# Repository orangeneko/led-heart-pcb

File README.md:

## About
LED heart. Surprise your soulmate!

## PCB

## Hardware
* MSP430F2370
* FT232RL & micro-usb for programming
* CR2032

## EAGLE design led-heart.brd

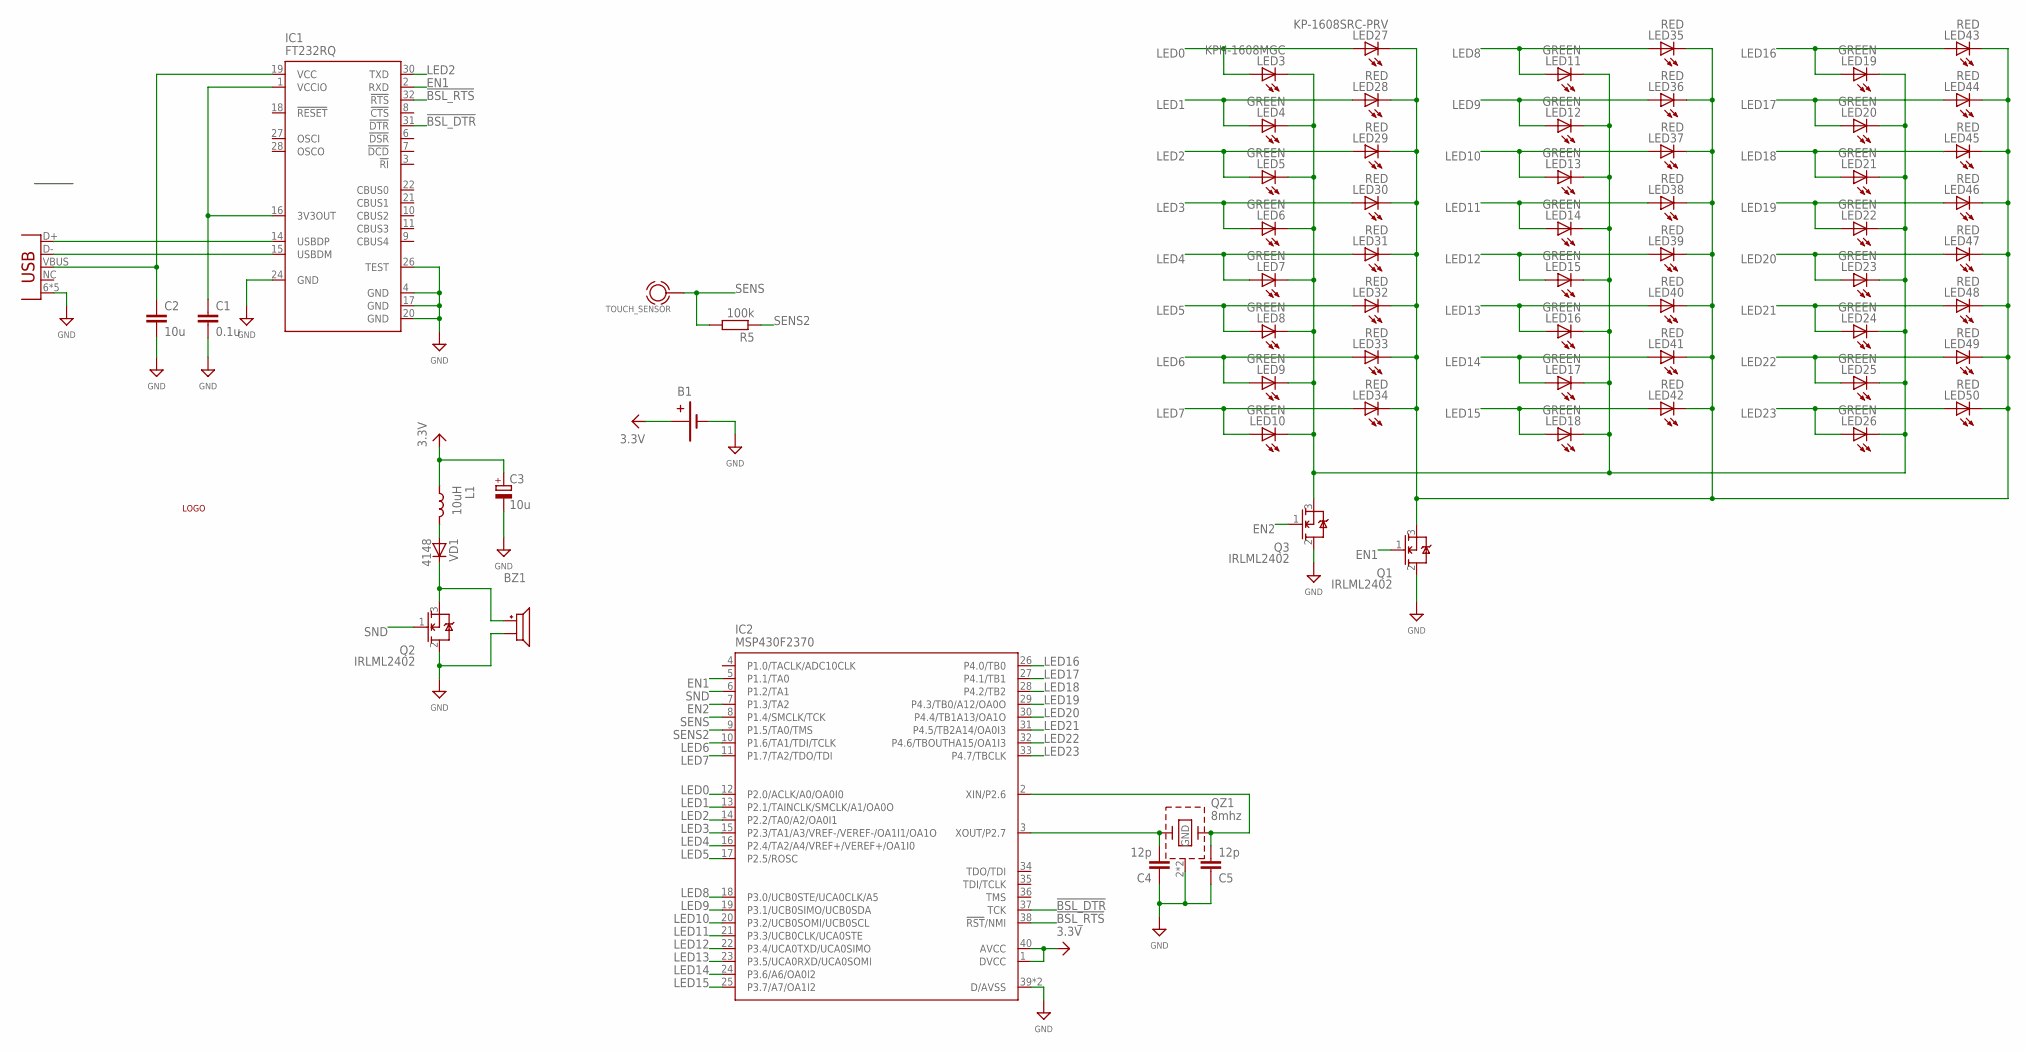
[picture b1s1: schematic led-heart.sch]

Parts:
B1: CR2032
BZ1: BUZZERHYG2575; HYG7525
C1: 0.1u; R0402
C2: 10u; R0603
C3: 10u; SMC_A
C4, C5: 12p; R0402
IC1: FT232RQ; QFN32
IC2: MSP430F2370; QFN40-6X6
L1: 10uH; C1812
LED3: KPH-1608MGC; LED0603
LED4, LED5, LED6, LED7, LED8, LED9, LED10, LED11, LED12, LED13, LED14, LED15, LED16, LED17, LED18, LED19, LED20, LED21, LED22, LED23, LED24, LED25, LED26: GREEN; LED0603
LED27: KP-1608SRC-PRV; LED0603
LED28, LED29, LED30, LED31, LED32, LED33, LED34, LED35, LED36, LED37, LED38, LED39, LED40, LED41, LED42, LED43, LED44, LED45, LED46, LED47, LED48, LED49, LED50: RED; LED0603
LOGO1: LOGO2
Q1, Q2, Q3: IRLML2402; SOT23
QZ1: 8mhz; 3225
R5: 100k; R0402
U$1: TOUCH_SENSOR
VD1: 4148; SOD123
X1: USBMICRO_B; USB_MICROB

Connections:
3.3V: B1.PLUS, C3.+, IC2.1 (DVCC), IC2.40 (AVCC), L1.1
5V: C2.1, IC1.19 (VCC), X1.VBUS
!BSL_DTR: IC1.31 (!DTR), IC2.37 (TCK)
!BSL_RTS: IC1.32 (!RTS), IC2.38 (!RST!/NMI)
BOOST: L1.2, VD1.A
EN1: IC1.2 (RXD), IC2.5 (P1.1/TA0), Q1.1 (G)
EN2: IC2.7 (P1.3/TA2), Q3.1 (G)
GND: B1.MINUS, BZ1.2 (M), C1.2, C2.2, C3.-, C4.1, C5.1, IC1.4 (GND), IC1.17 (GND), IC1.20 (GND), IC1.24 (GND), IC1.26 (TEST), IC2.39 (D/AVSS), IC2.EXP (D/AVSS), Q1.2 (S), Q2.2 (S), Q3.2 (S), QZ1.2 (GND), QZ1.4 (GND), X1.6 (GND), X1.7 (GND), X1.8 (GND), X1.9 (GND), X1.GND
LED0: IC2.12 (P2.0/ACLK/A0/OA0I0), LED3.A, LED27.A
LED1: IC2.13 (P2.1/TAINCLK/SMCLK/A1/OA0O), LED4.A, LED28.A
LED2: IC1.30 (TXD), IC2.14 (P2.2/TA0/A2/OA0I1), LED5.A, LED29.A
LED3: IC2.15 (P2.3/TA1/A3/VREF-/VEREF-/OA1I1/OA1O), LED6.A, LED30.A
LED4: IC2.16 (P2.4/TA2/A4/VREF+/VEREF+/OA1I0), LED7.A, LED31.A
LED5: IC2.17 (P2.5/ROSC), LED8.A, LED32.A
LED6: IC2.10 (P1.6/TA1/TDI/TCLK), LED9.A, LED33.A
LED7: IC2.11 (P1.7/TA2/TDO/TDI), LED10.A, LED34.A
LED8: IC2.18 (P3.0/UCB0STE/UCA0CLK/A5), LED11.A, LED35.A
LED9: IC2.19 (P3.1/UCB0SIMO/UCB0SDA), LED12.A, LED36.A
LED10: IC2.20 (P3.2/UCB0SOMI/UCB0SCL), LED13.A, LED37.A
LED11: IC2.21 (P3.3/UCB0CLK/UCA0STE), LED14.A, LED38.A
LED12: IC2.22 (P3.4/UCA0TXD/UCA0SIMO), LED15.A, LED39.A
LED13: IC2.23 (P3.5/UCA0RXD/UCA0SOMI), LED16.A, LED40.A
LED14: IC2.24 (P3.6/A6/OA0I2), LED17.A, LED41.A
LED15: IC2.25 (P3.7/A7/OA1I2), LED18.A, LED42.A
LED16: IC2.26 (P4.0/TB0), LED19.A, LED43.A
LED17: IC2.27 (P4.1/TB1), LED20.A, LED44.A
LED18: IC2.28 (P4.2/TB2), LED21.A, LED45.A
LED19: IC2.29 (P4.3/TB0/A12/OA0O), LED22.A, LED46.A
LED20: IC2.30 (P4.4/TB1A13/OA1O), LED23.A, LED47.A
LED21: IC2.31 (P4.5/TB2A14/OA0I3), LED24.A, LED48.A
LED22: IC2.32 (P4.6/TBOUTHA15/OA1I3), LED25.A, LED49.A
LED23: IC2.33 (P4.7/TBCLK), LED26.A, LED50.A
LINE1: LED27.C, LED28.C, LED29.C, LED30.C, LED31.C, LED32.C, LED33.C, LED34.C, LED35.C, LED36.C, LED37.C, LED38.C, LED39.C, LED40.C, LED41.C, LED42.C, LED43.C, LED44.C, LED45.C, LED46.C, LED47.C, LED48.C, LED49.C, LED50.C, Q1.3 (D)
LINE2: LED3.C, LED4.C, LED5.C, LED6.C, LED7.C, LED8.C, LED9.C, LED10.C, LED11.C, LED12.C, LED13.C, LED14.C, LED15.C, LED16.C, LED17.C, LED18.C, LED19.C, LED20.C, LED21.C, LED22.C, LED23.C, LED24.C, LED25.C, LED26.C, Q3.3 (D)
SENS: IC2.8 (P1.4/SMCLK/TCK), R5.2, U$1.CON
SENS2: IC2.9 (P1.5/TA0/TMS), R5.1
SND: IC2.6 (P1.2/TA1), Q2.1 (G)
USB+DP: IC1.14 (USBDP), X1.D+
USB_DM: IC1.15 (USBDM), X1.D-
VCCIO: C1.1, IC1.1 (VCCIO), IC1.16 (3V3OUT)
V_SND: BZ1.1, Q2.3 (D), VD1.C
XIN: C5.2, IC2.2 (XIN/P2.6), QZ1.1
XOUT: C4.2, IC2.3 (XOUT/P2.7), QZ1.3 (2)

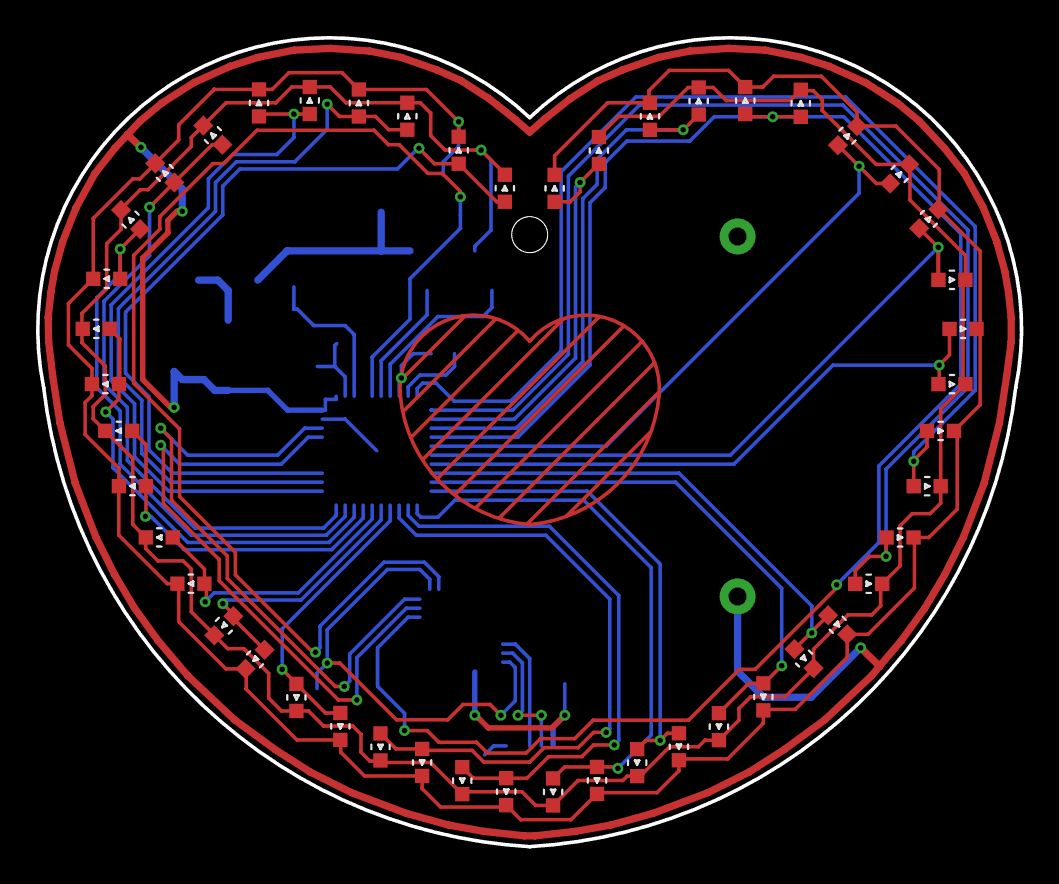
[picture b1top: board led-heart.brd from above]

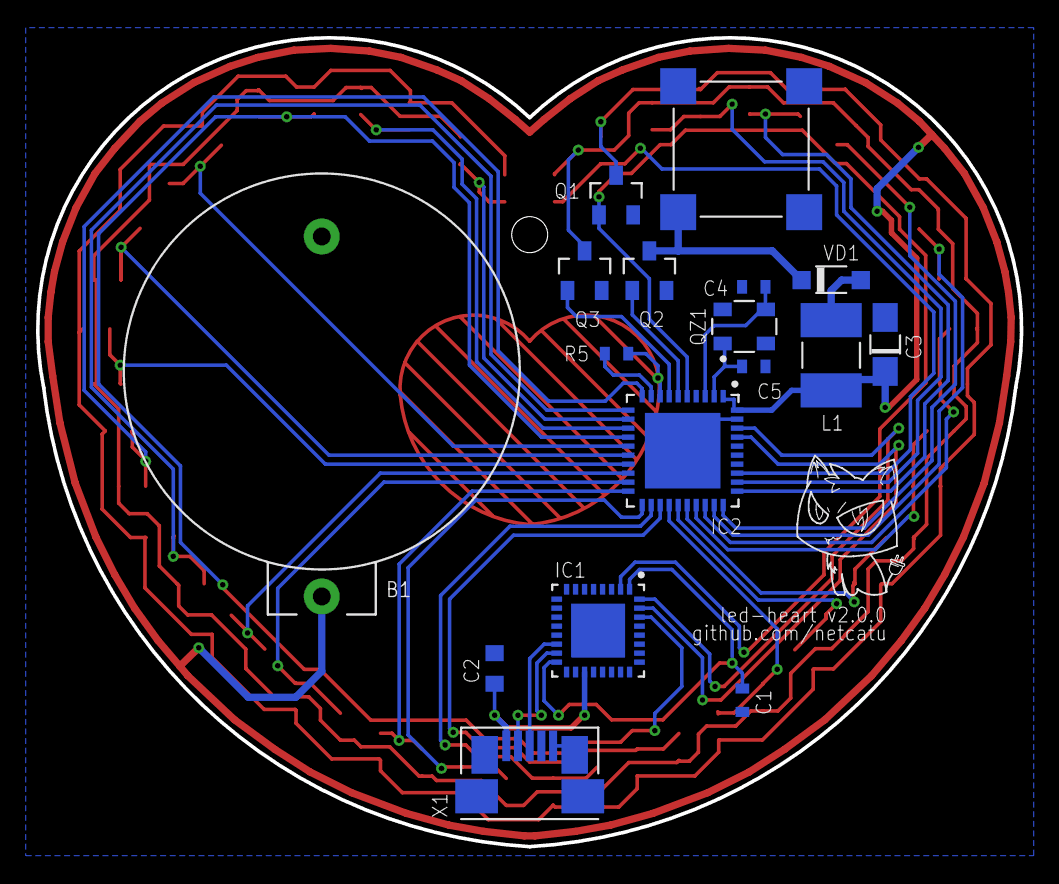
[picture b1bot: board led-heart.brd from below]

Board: 2 copper layers, 54.7 x 44.9 mm, 67 parts (18 on the bottom side), 43 nets.

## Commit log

2018-09-01 first template
2018-09-01 release, fix schematic, pcb, silk, docs
2018-09-20 new design, qfn packages, buzzer for sound
